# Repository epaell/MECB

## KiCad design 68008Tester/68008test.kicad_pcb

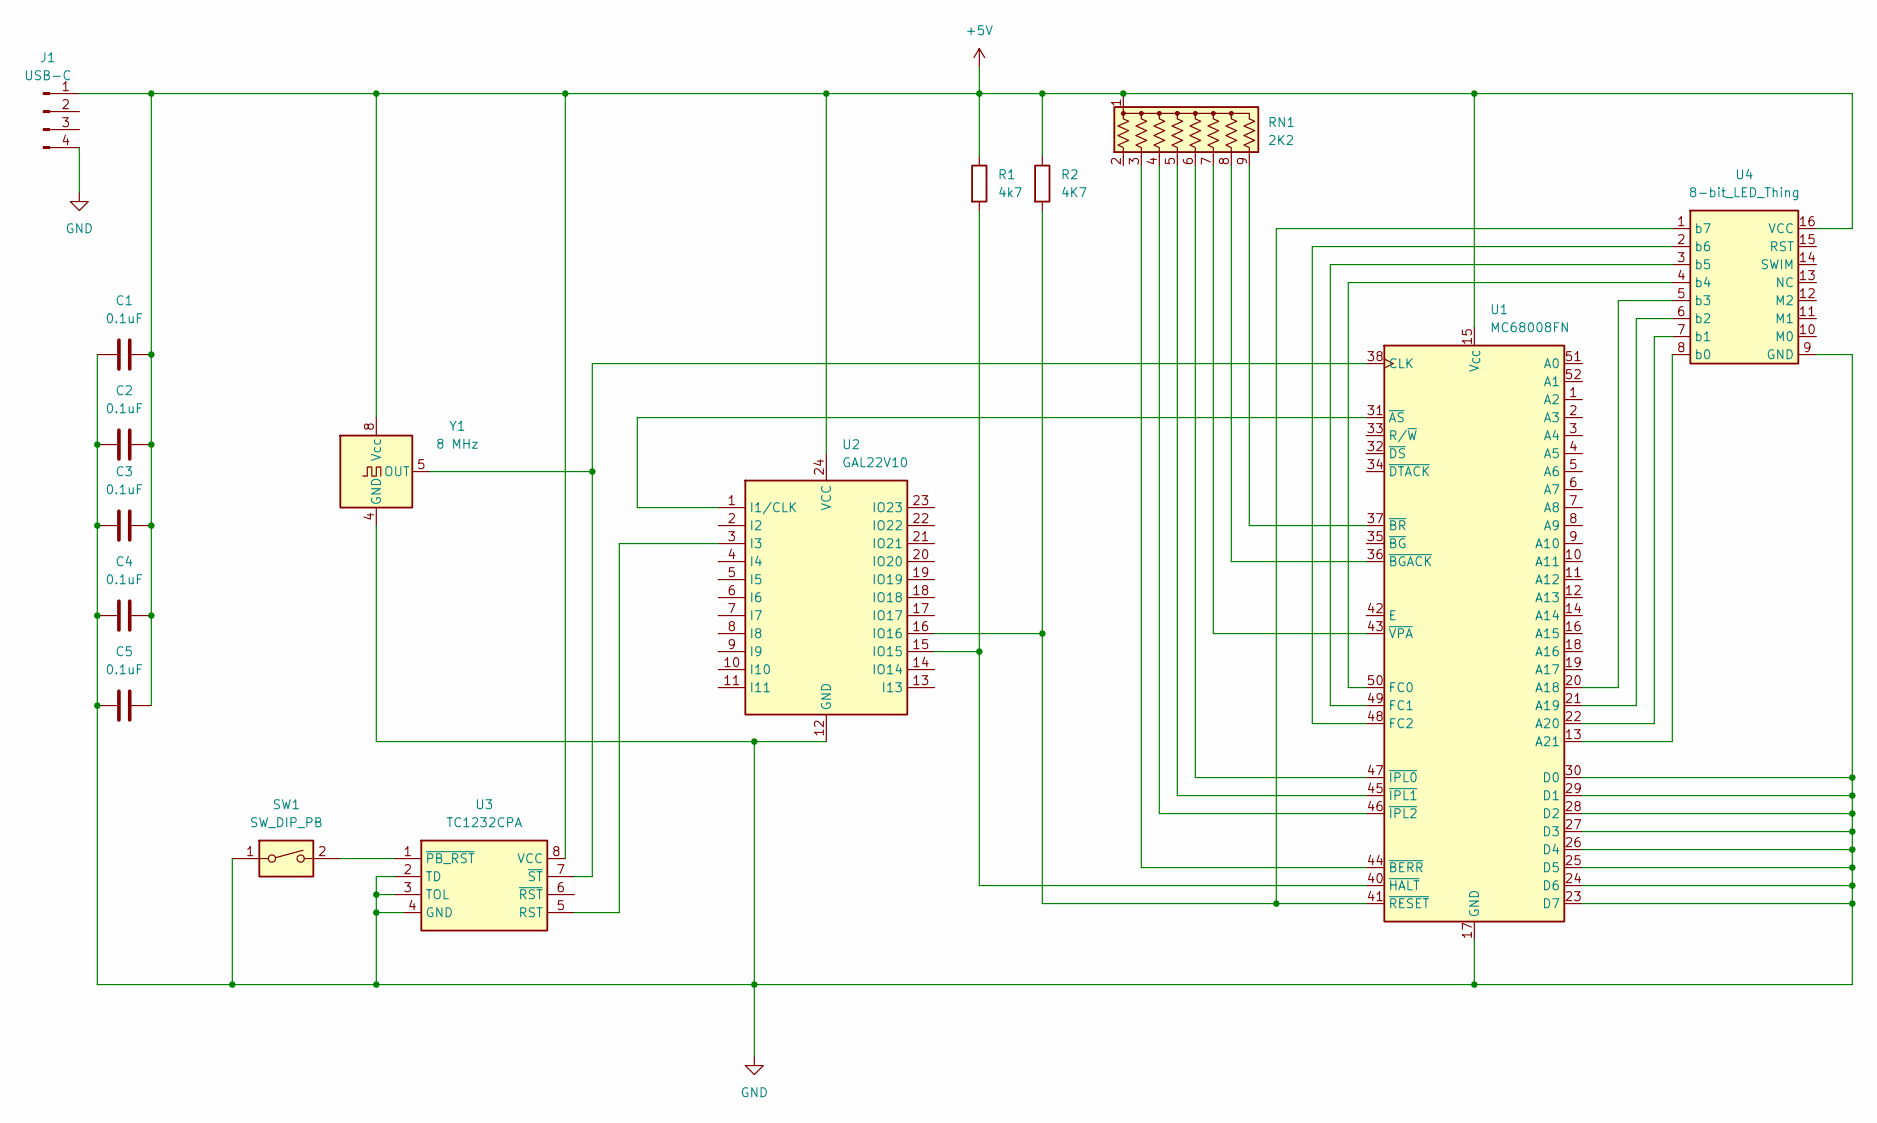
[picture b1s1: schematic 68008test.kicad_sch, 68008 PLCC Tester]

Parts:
C1, C2, C3, C4, C5: 0.1uF; C_Disc_D6.0mm_W2.5mm_P5.00mm
J1: USB-C; PinHeader_1x04_P2.54mm_Vertical
R1: 4k7; R_Axial_DIN0309_L9.0mm_D3.2mm_P12.70mm_Horizontal
R2: 4K7; R_Axial_DIN0309_L9.0mm_D3.2mm_P12.70mm_Horizontal
RN1: 2K2; R_Array_SIP9
SW1: SW_DIP_PB; SW_Tactile_Straight_KSA0Axx1LFTR
U1: MC68008FN; PLCC-52_THT-Socket
U2: GAL22V10; DIP-24_W7.62mm_Socket_LongPads
U3: TC1232CPA; DIP-8_W7.62mm_Socket_LongPads
U4: 8-bit_LED_Thing; DIP-16_W12mm_Socket_LongPads
Y1: 8 MHz; DIP-8_W7.62mm_Socket_LongPads

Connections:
+5V: C1.2, C2.2, C3.2, C4.2, C5.2, J1.1, R1.1, R2.1, RN1.1 (common), U1.15 (V_{CC}), U2.24 (VCC), U3.8 (VCC), U4.16 (VCC), Y1.8 (Vcc)
GND: C1.1, C2.1, C3.1, C4.1, C5.1, J1.4, SW1.1, U1.17 (GND), U1.23 (D7), U1.24 (D6), U1.25 (D5), U1.26 (D4), U1.27 (D3), U1.28 (D2), U1.29 (D1), U1.30 (D0), U1.39 (GND), U2.12 (GND), U3.2 (TD), U3.3 (TOL), U3.4 (GND), U4.9 (GND), Y1.4 (GND)
unnamed: RN1.3 (R2), U1.44 (~BERR)
unnamed: RN1.4 (R3), U1.46 (~IPL2)
unnamed: RN1.5 (R4), U1.45 (~IPL1)
unnamed: RN1.6 (R5), U1.47 (~IPL0)
unnamed: RN1.7 (R6), U1.43 (~VPA)
unnamed: RN1.8 (R7), U1.36 (~BGACK)
unnamed: RN1.9 (R8), U1.37 (~BR)
unnamed: U1.20 (A18), U4.5 (b3)
unnamed: U1.21 (A19), U4.6 (b2)
unnamed: U1.22 (A20), U4.7 (b1)
unnamed: U1.13 (A21), U4.8 (b0)
unnamed: U1.38 (CLK), U3.7 (~ST), Y1.5 (OUT)
unnamed: U1.50 (FC0), U4.4 (b4)
unnamed: U1.49 (FC1), U4.3 (b5)
unnamed: U1.48 (FC2), U4.2 (b6)
unnamed: U1.31 (~AS), U2.1 (I1/CLK)
unnamed: R1.2, U1.40 (~HALT), U2.15 (IO15)
unnamed: R2.2, U1.41 (~RESET), U2.16 (IO16), U4.1 (b7)
unnamed: U2.3 (I3), U3.5 (RST)
unnamed: SW1.2, U3.1 (~PB_RST)

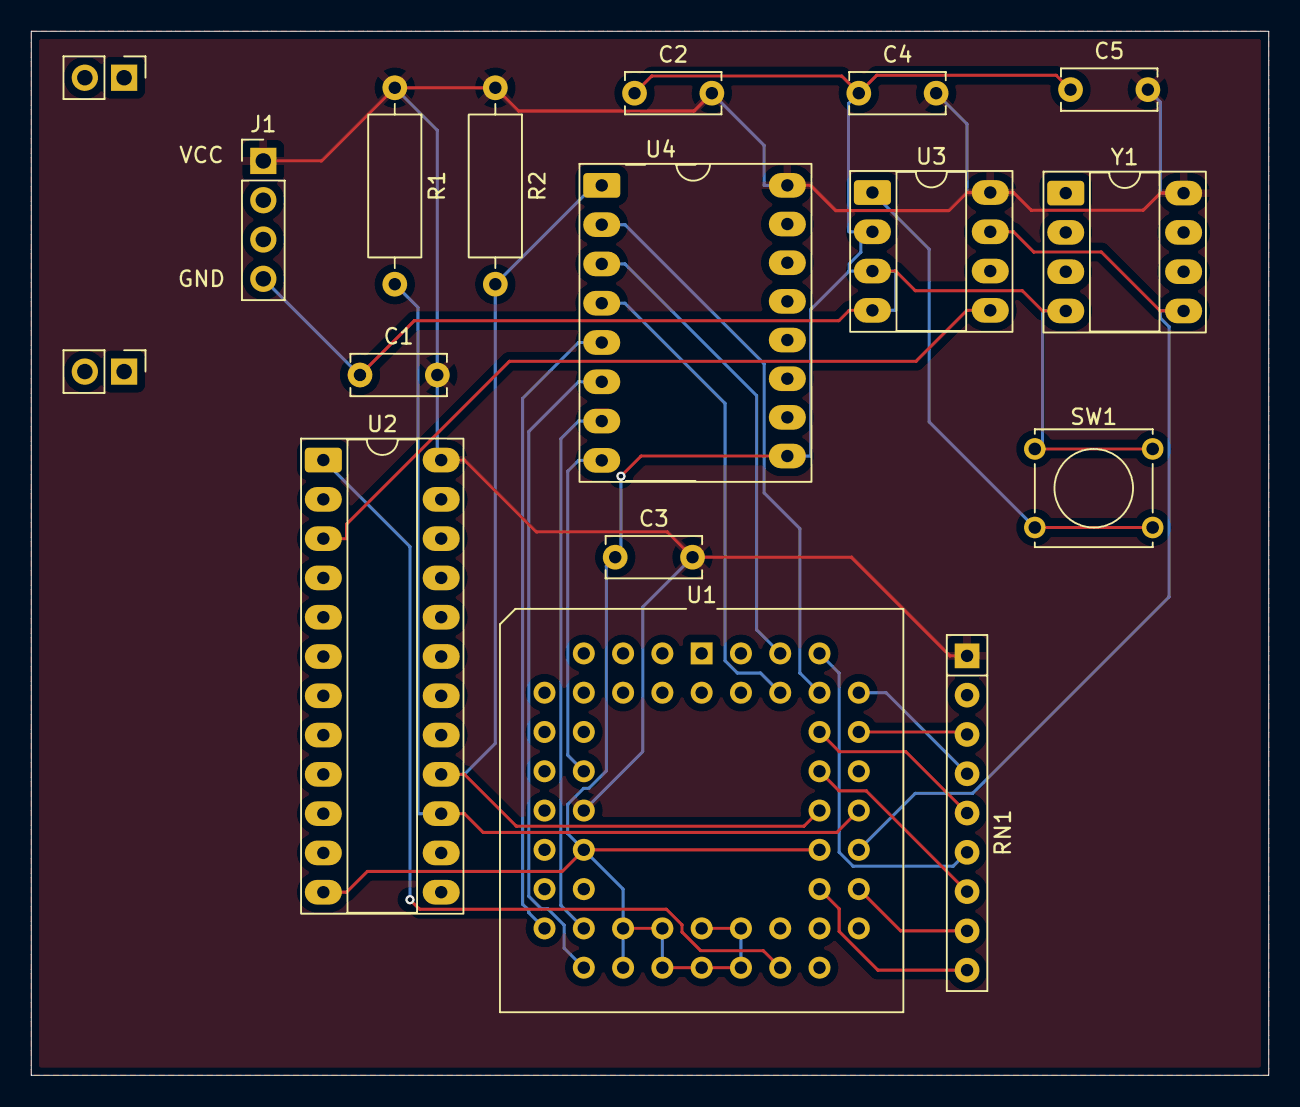
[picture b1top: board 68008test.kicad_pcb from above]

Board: 2 copper layers, 80.0 x 67.5 mm, 16 parts (0 on the bottom side), 22 nets.

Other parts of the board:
BRACE2: PinHeader_1x02_P2.54mm_Vertical

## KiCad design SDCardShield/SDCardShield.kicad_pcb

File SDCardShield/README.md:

# SDCardShield
A version of the SD Card shield that was originally developed by Corsham Technologies for the SWTPC. It has been modified to work with the MECB I/O board (PIA port) and makes use of Adafruit modules to implement the realtime clock:

https://core-electronics.com.au/adafruit-ds3231-precision-rtc-breakout.html

and microSD interface:

https://core-electronics.com.au/microsd-card-breakout-board.html

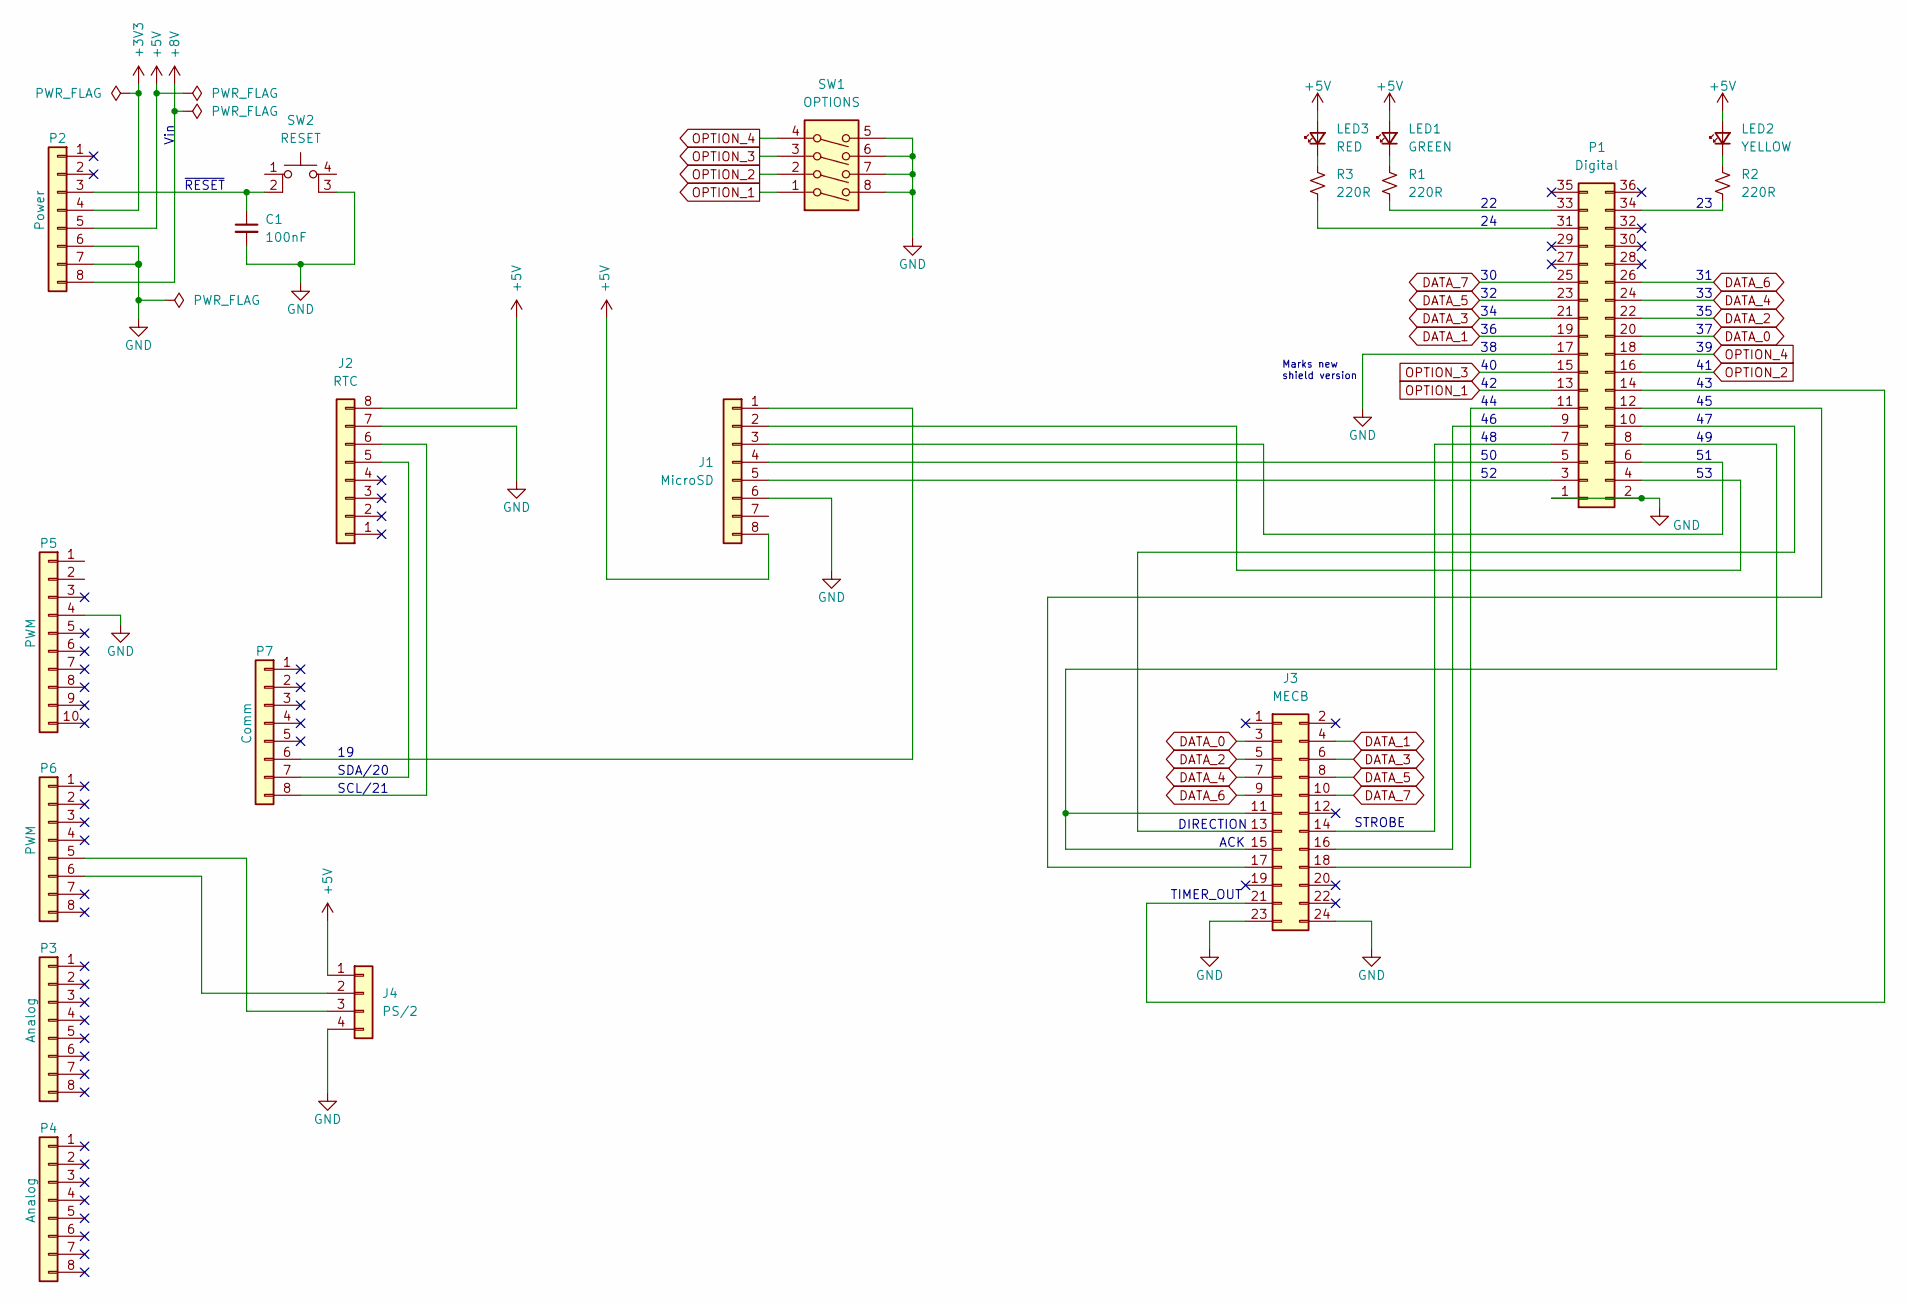
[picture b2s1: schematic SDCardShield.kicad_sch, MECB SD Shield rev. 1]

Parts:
C1: 100nF; C_Disc_D5.0mm_W2.5mm_P2.50mm; LCSC C2762593
J1: MicroSD; PinSocket_1x08_P2.54mm_Vertical
J2: RTC; PinSocket_1x08_P2.54mm_Vertical
J3: MECB; IDC-Header_2x12_P2.54mm_Vertical
J4: PS/2; PinHeader_1x04_P2.54mm_Vertical
LED1: GREEN; LED_D5.0mm; PART SML-D12P8WT86; LCSC C510026
LED2: YELLOW; LED_D5.0mm; PART SML-D12Y8WT86; LCSC C2840179
LED3: RED; LED_D5.0mm; PART SML-D12V8WT86; LCSC C2693607
P1: Digital; PinSocket_2x18_P2.54mm_Vertical
P2: Power; PinSocket_1x08_P2.54mm_Vertical
P3, P4: Analog; PinSocket_1x08_P2.54mm_Vertical
P5: PWM; PinSocket_1x10_P2.54mm_Vertical
P6: PWM; PinSocket_1x08_P2.54mm_Vertical
P7: Comm; PinSocket_1x08_P2.54mm_Vertical
R1, R2, R3: 220R; R_Axial_DIN0207_L6.3mm_D2.5mm_P10.16mm_Horizontal; LCSC C270843
SW1: OPTIONS; SW_DIP_SPSTx04_Slide_9.78x12.34mm_W7.62mm_P2.54mm; LCSC C54950
SW2: RESET; SW_Push_2P1T_Toggle_CK_PVA1xxH1xxxxxxV2

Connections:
+3V3: P2.4
+5V: J1.8, J2.8, J4.1, LED1.2 (A), LED2.2 (A), LED3.2 (A), P2.5
+8V: P2.8
DATA_0: J3.3, P1.20
DATA_1: J3.4, P1.19
DATA_2: J3.5, P1.22
DATA_3: J3.6, P1.21
DATA_4: J3.7, P1.24
DATA_5: J3.8, P1.23
DATA_6: J3.9, P1.26
DATA_7: J3.10, P1.25
GND: C1.2, J1.6, J2.7, J3.23, J3.24, J4.4, P1.1, P1.2, P1.17, P2.6, P2.7, P5.4, SW1.5, SW1.6, SW1.7, SW1.8, SW2.3 (K)
unnamed: J1.1, P7.6
unnamed: J1.2, P1.4
unnamed: J1.3, P1.6
unnamed: J1.4, P1.5
unnamed: J1.5, P1.3
unnamed: J2.5, P7.7
unnamed: J2.6, P7.8
unnamed: J3.11, J3.15, P1.8
unnamed: J3.13, P1.10
unnamed: J3.14, P1.7
unnamed: J3.16, P1.9
unnamed: J3.17, P1.12
unnamed: J3.18, P1.11
unnamed: J3.21, P1.14
unnamed: J4.2, P6.6
unnamed: J4.3, P6.5
unnamed: LED1.1 (K), R1.1
unnamed: LED2.1 (K), R2.1
unnamed: LED3.1 (K), R3.1
unnamed: P1.31, R3.2
unnamed: P1.33, R1.2
unnamed: P1.34, R2.2
unnamed: C1.1, P2.3, SW2.2
OPTION_1: P1.13, SW1.1
OPTION_2: P1.16, SW1.2
OPTION_3: P1.15, SW1.3
OPTION_4: P1.18, SW1.4

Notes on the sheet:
TIMER_OUT
Vin
~{RESET}
SDA/20
STROBE
DIRECTION
SCL/21
Marks new shield version
ACK

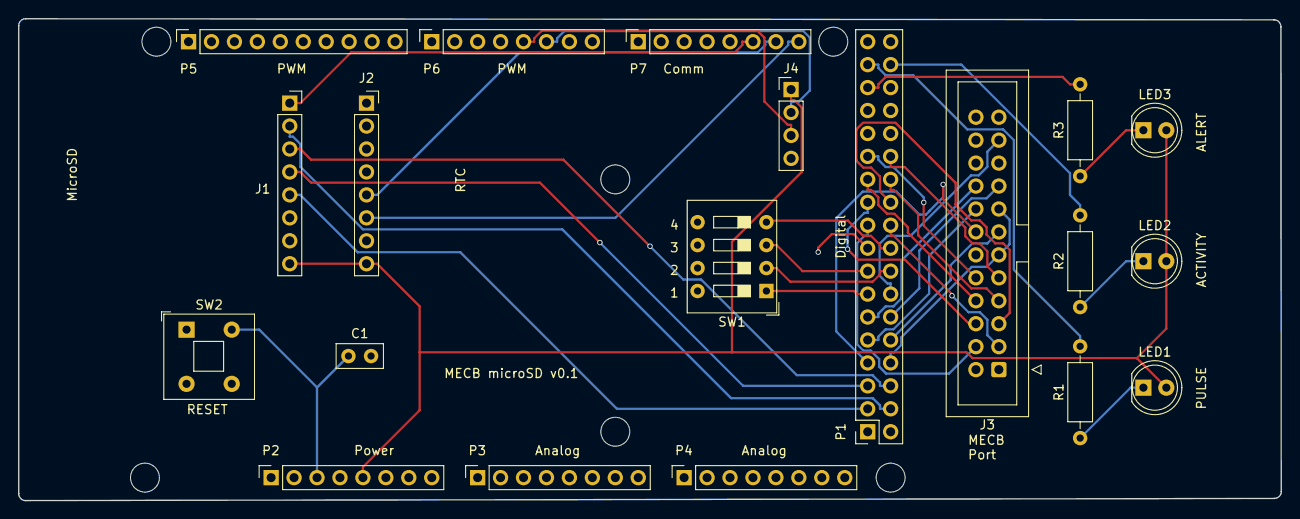
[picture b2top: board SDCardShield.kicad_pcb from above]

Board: 2 copper layers, 139.8 x 53.3 mm, 26 parts (0 on the bottom side), 37 nets.

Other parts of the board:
MH1, MH2, MH3, MH4, MH5, MH6: MountingHole_3.2mm
